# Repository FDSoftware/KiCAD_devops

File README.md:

# KiCAD_devops
sample proyect for kicad automation in GitHub CI/CD

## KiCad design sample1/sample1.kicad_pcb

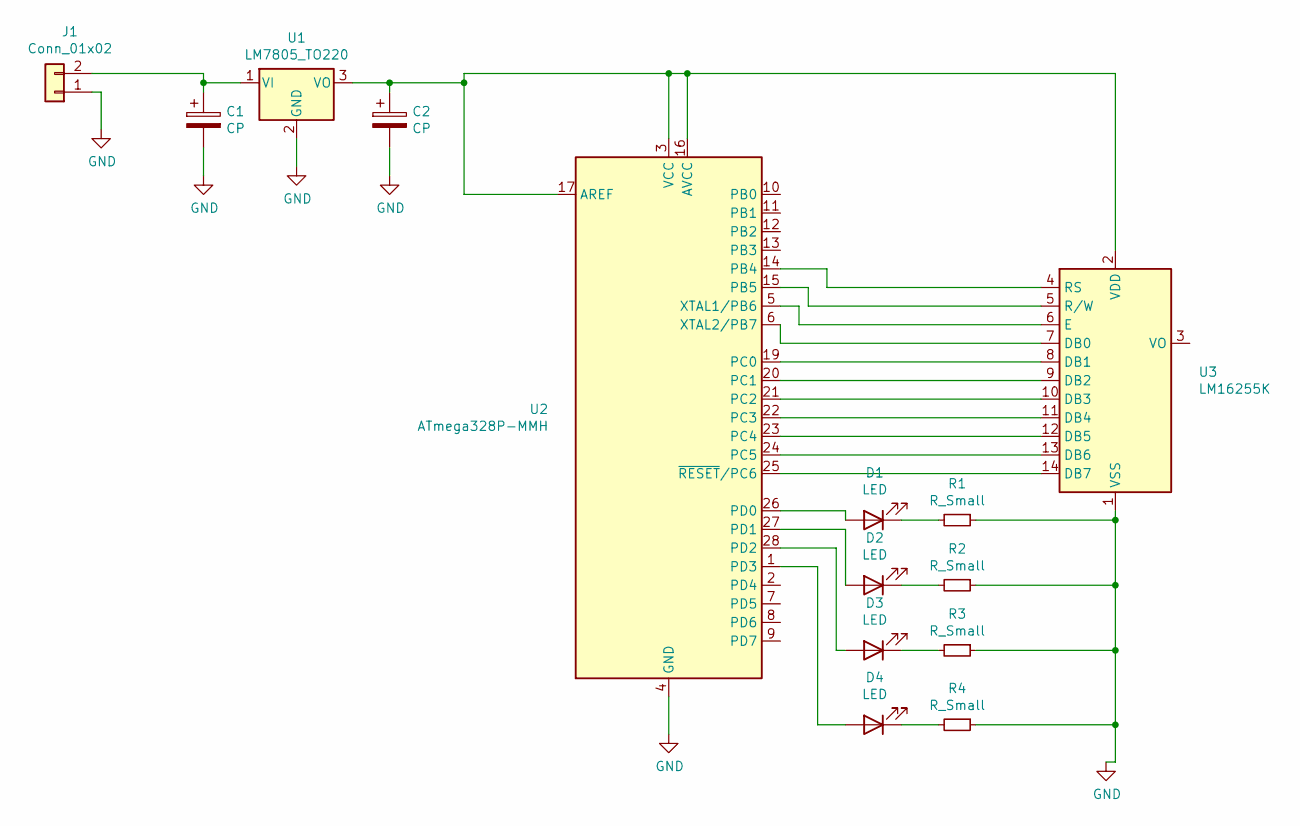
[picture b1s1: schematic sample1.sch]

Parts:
C1, C2: CP; CP_Radial_D5.0mm_P2.50mm
D1, D2, D3, D4: LED; LED_D1.8mm_W1.8mm_H2.4mm_Horizontal_O1.27mm_Z1.6mm
J1: Conn_01x02; PinHeader_1x02_P1.00mm_Vertical_SMD_Pin1Left
R1, R2, R3, R4: R_Small; R_Axial_DIN0204_L3.6mm_D1.6mm_P7.62mm_Horizontal
U1: LM7805_TO220; TO-220-3_Vertical
U2: ATmega328P-MMH; QFN-28-1EP_4x4mm_P0.45mm_EP2.4x2.4mm
U3: LM16255K; LM16255

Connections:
GND: C1.2, C2.2, J1.1, R1.1, R2.1, R3.1, R4.1, U1.2 (GND), U2.4 (GND), U2.18 (GND), U2.29 (GND), U3.1 (VSS)
unnamed: C1.1, J1.2, U1.1 (VI)
unnamed: C2.1, U1.3 (VO), U2.3 (VCC), U2.16 (AVCC), U2.17 (AREF), U3.2 (VDD)
unnamed: D1.1 (K), R1.2
unnamed: D1.2 (A), U2.26 (PD0)
unnamed: D2.1 (K), R2.2
unnamed: D2.2 (A), U2.27 (PD1)
unnamed: D3.1 (K), R3.2
unnamed: D3.2 (A), U2.28 (PD2)
unnamed: D4.1 (K), R4.2
unnamed: D4.2 (A), U2.1 (PD3)
unnamed: U2.5 (XTAL1/PB6), U3.6 (E)
unnamed: U2.6 (XTAL2/PB7), U3.7 (DB0)
unnamed: U2.14 (PB4), U3.4 (RS)
unnamed: U2.15 (PB5), U3.5 (R/W)
unnamed: U2.19 (PC0), U3.8 (DB1)
unnamed: U2.20 (PC1), U3.9 (DB2)
unnamed: U2.21 (PC2), U3.10 (DB3)
unnamed: U2.22 (PC3), U3.11 (DB4)
unnamed: U2.23 (PC4), U3.12 (DB5)
unnamed: U2.24 (PC5), U3.13 (DB6)
unnamed: U2.25 (~RESET~/PC6), U3.14 (DB7)

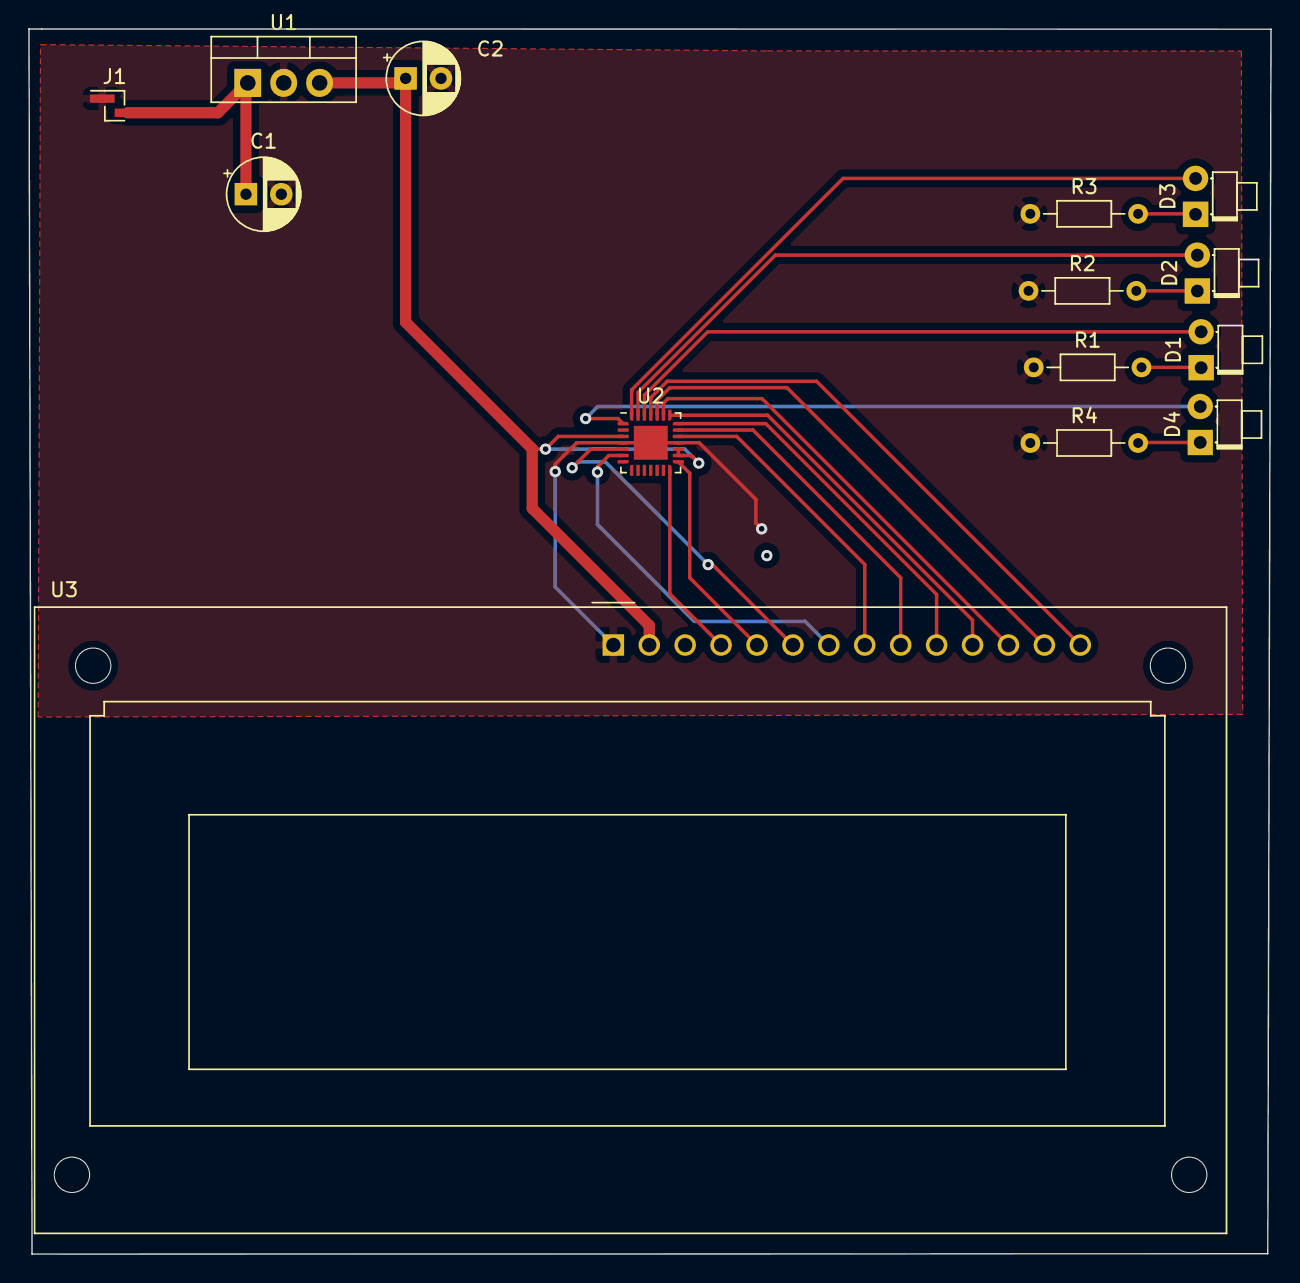
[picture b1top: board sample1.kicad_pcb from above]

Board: 2 copper layers, 87.8 x 86.6 mm, 14 parts (0 on the bottom side), 22 nets.

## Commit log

2020-06-29 init
2020-06-30 test pbcnew python
2020-06-30 re-test
2020-06-30 sudo powa
2020-06-30 update?
2020-06-30 fix ci
2020-06-30 eval kaker fix
2020-06-30 test
2020-06-30 final test
2020-06-30 upload workflow
2020-06-30 fix artifacts
2020-06-30 upload X display env
2020-06-30 lo' espacio
2020-06-30 update xvfb
2020-06-30 clean apt
2020-06-30 add inkscape
2020-06-30 remove png
2020-06-30 remove svg path
2020-06-30 refix artifact
